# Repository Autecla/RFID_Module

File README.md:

# Módulo de Leitura de cartões
Nesse módulo é feito a leitura dos cartões RFID através de uma matriz de leitores formada por 4 leitores RFID e 1 Arduino pro mini, que envia as informações dos cartões para o módulo de controle e comunicação, via serial.

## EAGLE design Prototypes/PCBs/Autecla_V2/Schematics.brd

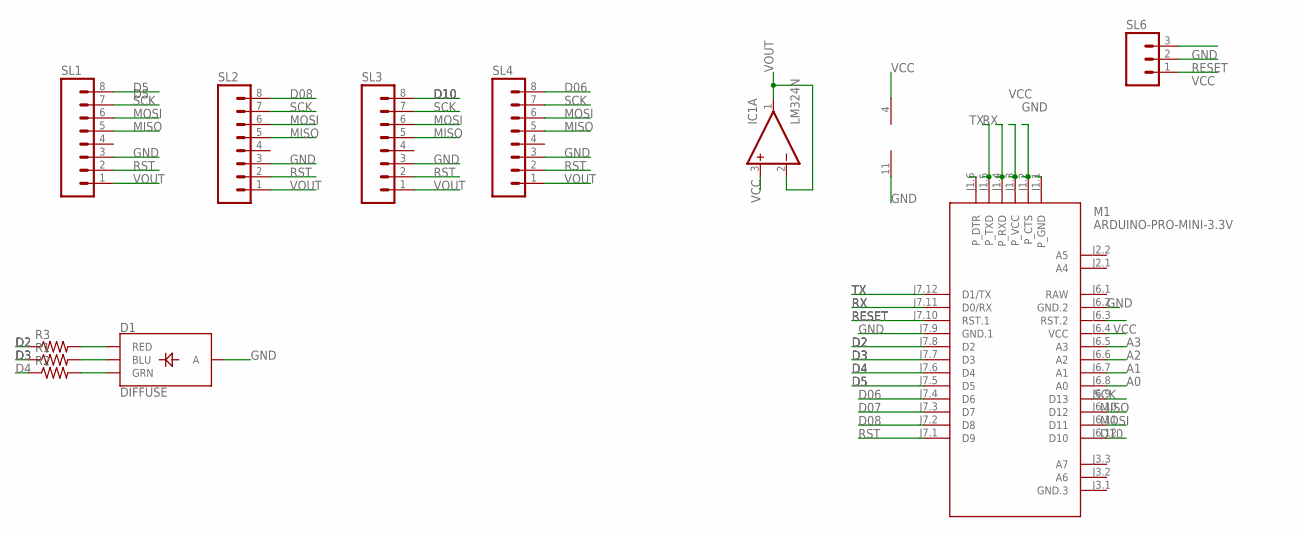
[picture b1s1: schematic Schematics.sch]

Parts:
D1: DIFFUSE; LED-RGB-THRU
IC1: LM324N; DIL14
M1: ARDUINO-PRO-MINI-3.3V; ARDUINO-PRO-MINI
R1, R2, R3: R-US_0204/7; 0204/7
SL1, SL2, SL3, SL4: M08; 08P
SL6: M03; 03P

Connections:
A0: M1.J6.8 (A0)
A1: M1.J6.7 (A1)
A2: M1.J6.6 (A2)
A3: M1.J6.5 (A3)
D2: M1.J7.8 (D2), R3.1
D3: M1.J7.7 (D3), R1.1
D4: M1.J7.6 (D4), R2.1
D5: M1.J7.5 (D5), SL1.8
D06: M1.J7.4 (D6), SL4.8
D07: M1.J7.3 (D7)
D08: M1.J7.2 (D8), SL2.8
D10: M1.J6.12 (D10), SL3.8
GND: D1.2 (A), IC1.11 (V-), M1.J1.2 (P_CTS), M1.J6.2 (GND.2), M1.J7.9 (GND.1), SL1.3, SL2.3, SL3.3, SL4.3, SL6.3
MISO: M1.J6.10 (D12), SL1.5, SL2.5, SL3.5, SL4.5
MOSI: M1.J6.11 (D11), SL1.6, SL2.6, SL3.6, SL4.6
unnamed: D1.1 (RED), R3.2
unnamed: D1.3 (GRN), R2.2
unnamed: D1.4 (BLU), R1.2
RAW: M1.J6.1 (RAW)
RESET: M1.J7.10 (RST.1), SL6.2
RST: M1.J7.1 (D9), SL1.2, SL2.2, SL3.2, SL4.2
RX: M1.J1.4 (P_RXD), M1.J7.11 (D0/RX)
SCK: M1.J6.9 (D13), SL1.7, SL2.7, SL3.7, SL4.7
TX: M1.J1.5 (P_TXD), M1.J7.12 (D1/TX)
VCC: IC1.3 (+IN), IC1.4 (V+), M1.J1.3 (P_VCC), M1.J6.4 (VCC), SL6.1
VOUT: IC1.1 (OUT), IC1.2 (-IN), SL1.1, SL2.1, SL3.1, SL4.1

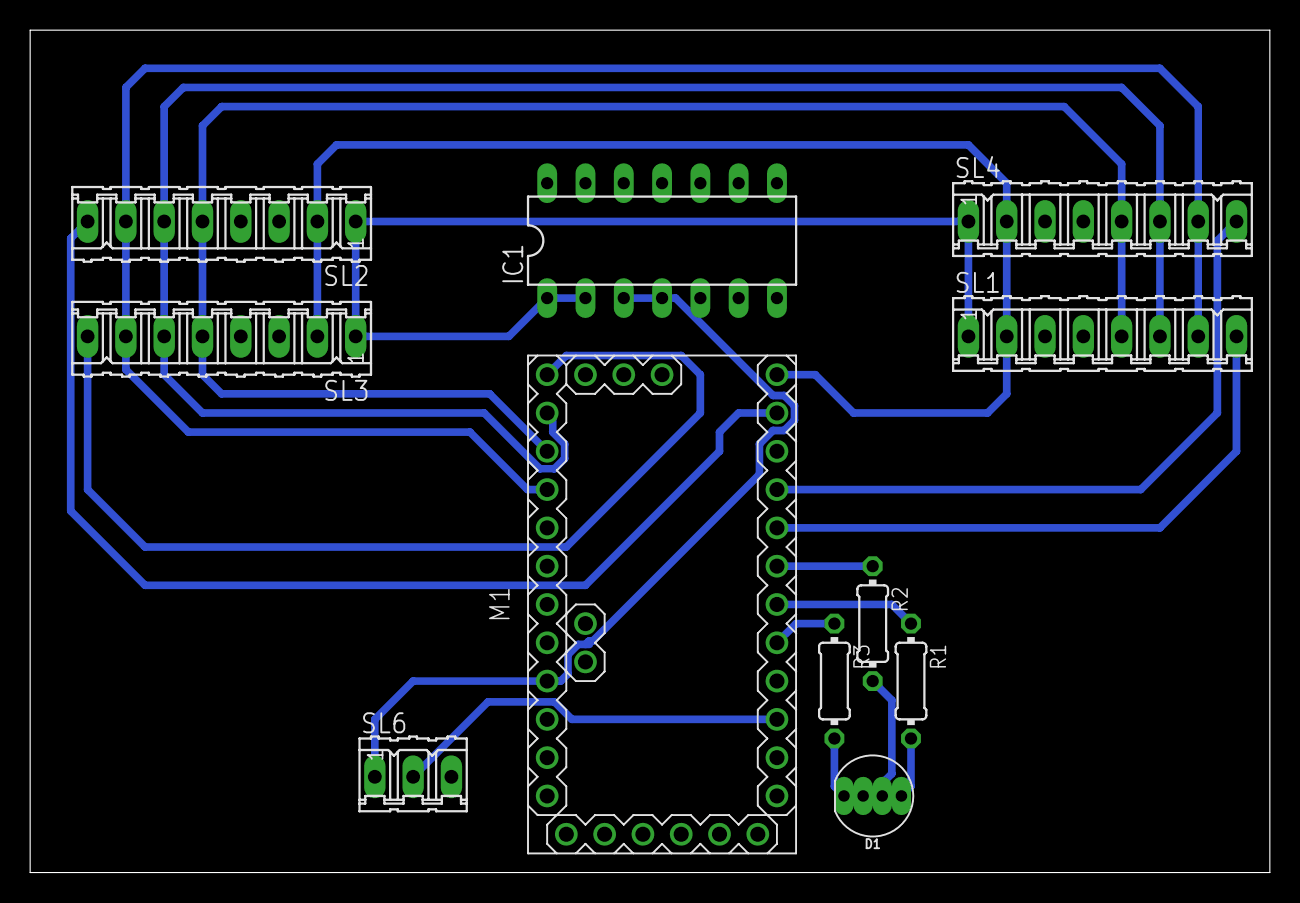
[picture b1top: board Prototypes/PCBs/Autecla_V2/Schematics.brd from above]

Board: 2 copper layers, 82.2 x 55.9 mm, 11 parts (0 on the bottom side), 20 nets.

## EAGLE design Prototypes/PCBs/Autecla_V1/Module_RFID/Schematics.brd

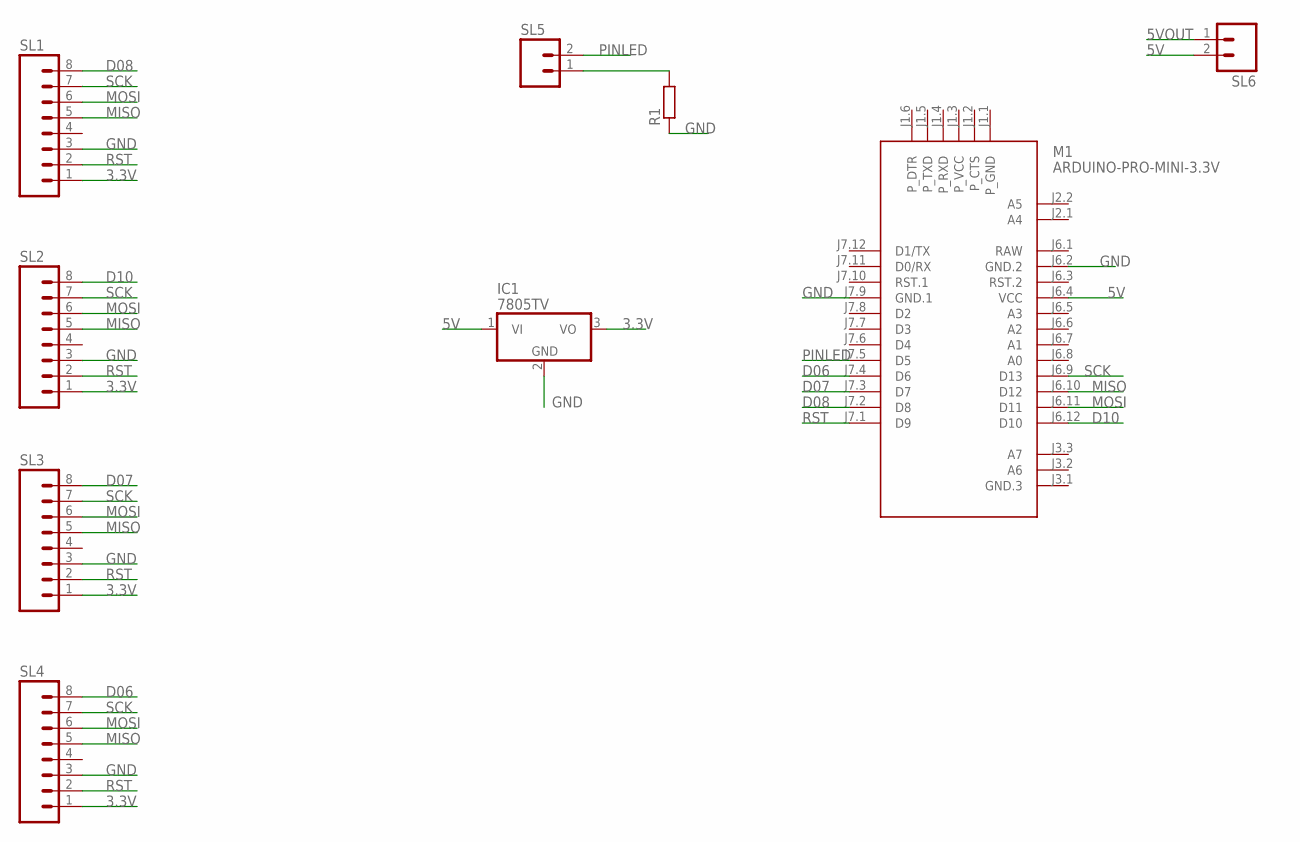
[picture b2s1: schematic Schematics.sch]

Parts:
IC1: 7805TV; TO220V
M1: ARDUINO-PRO-MINI-3.3V; ARDUINO-PRO-MINI
R1: R0204/7; 0204/7
SL1, SL2, SL3, SL4: M08; 08P
SL5, SL6: M02; 02P

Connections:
3.3V: IC1.3 (VO), SL1.1, SL2.1, SL3.1, SL4.1
5V: IC1.1 (VI), M1.J6.4 (VCC), SL6.2
5VOUT: SL6.1
D06: M1.J7.4 (D6), SL4.8
D07: M1.J7.3 (D7), SL3.8
D08: M1.J7.2 (D8), SL1.8
D10: M1.J6.12 (D10), SL2.8
GND: IC1.2 (GND), M1.J6.2 (GND.2), M1.J7.9 (GND.1), R1.1, SL1.3, SL2.3, SL3.3, SL4.3
MISO: M1.J6.10 (D12), SL1.5, SL2.5, SL3.5, SL4.5
MOSI: M1.J6.11 (D11), SL1.6, SL2.6, SL3.6, SL4.6
unnamed: R1.2, SL5.1
PINLED: M1.J7.5 (D5), SL5.2
RAW: M1.J6.1 (RAW)
RST: M1.J7.1 (D9), SL1.2, SL2.2, SL3.2, SL4.2
SCK: M1.J6.9 (D13), SL1.7, SL2.7, SL3.7, SL4.7

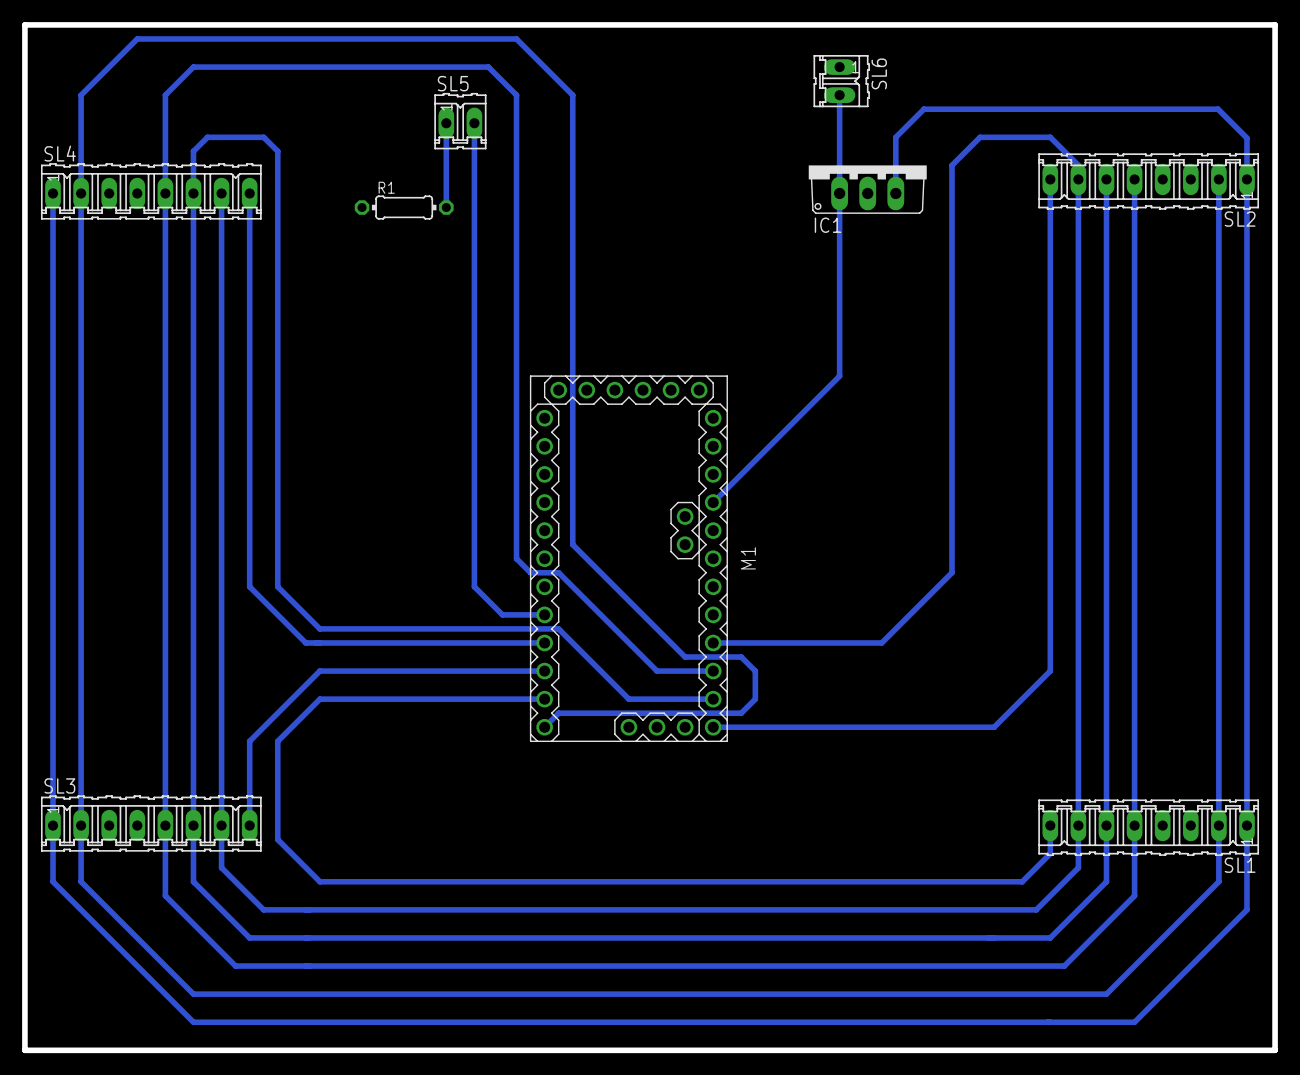
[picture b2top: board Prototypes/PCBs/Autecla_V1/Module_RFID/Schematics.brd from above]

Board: 2 copper layers, 113.0 x 92.7 mm, 9 parts (0 on the bottom side), 13 nets.

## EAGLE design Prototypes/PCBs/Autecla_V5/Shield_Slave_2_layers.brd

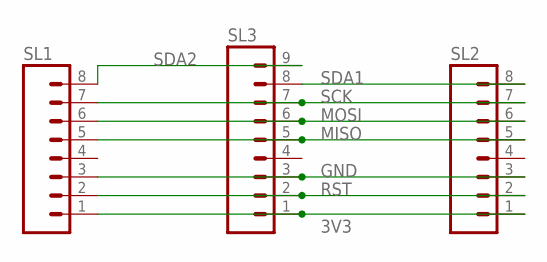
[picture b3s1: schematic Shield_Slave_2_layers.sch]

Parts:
SL1, SL2: M08; 08P
SL3: M09; 09P

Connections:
3V3: SL1.1, SL2.1, SL3.1
GND: SL1.3, SL2.3, SL3.3
MISO: SL1.5, SL2.5, SL3.5
MOSI: SL1.6, SL2.6, SL3.6
RST: SL1.2, SL2.2, SL3.2
SCK: SL1.7, SL2.7, SL3.7
SDA1: SL2.8, SL3.8
SDA2: SL1.8, SL3.9

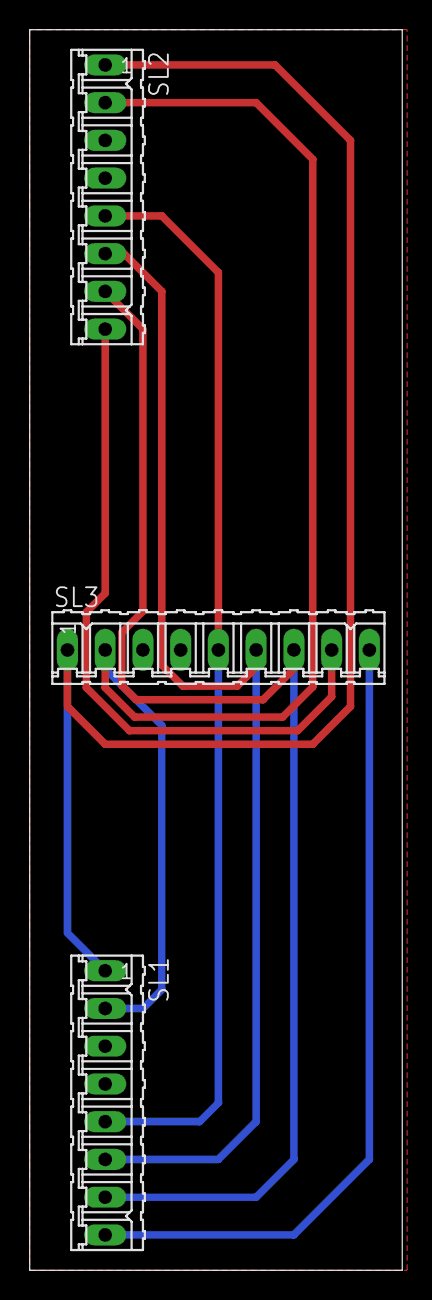
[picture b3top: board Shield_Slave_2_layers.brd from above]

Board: 2 copper layers, 25.1 x 83.5 mm, 3 parts (0 on the bottom side), 8 nets.

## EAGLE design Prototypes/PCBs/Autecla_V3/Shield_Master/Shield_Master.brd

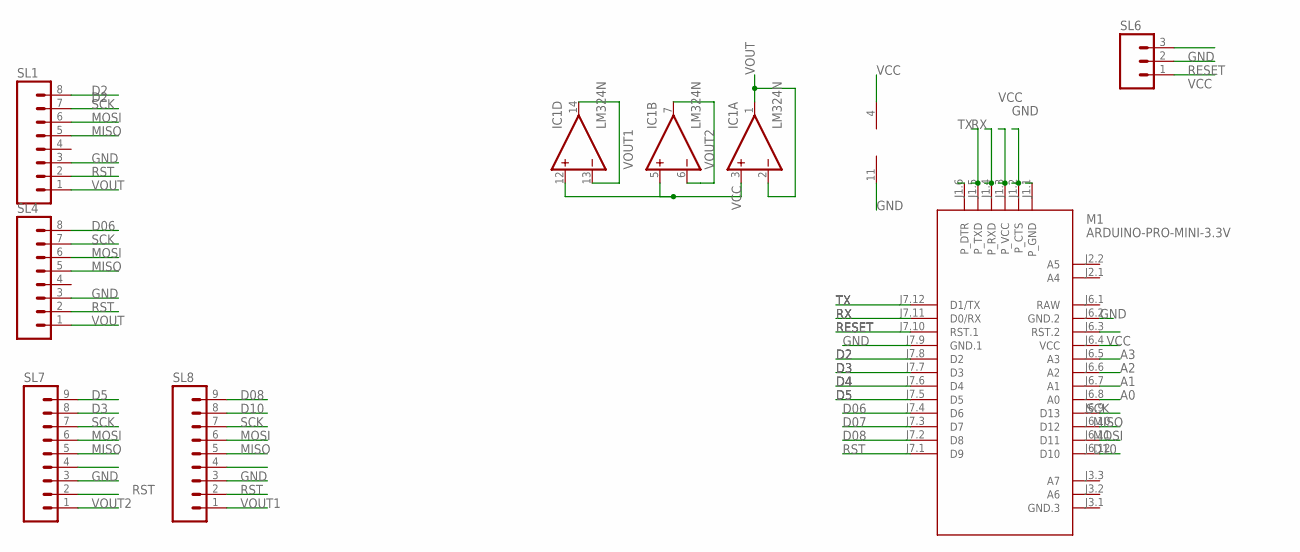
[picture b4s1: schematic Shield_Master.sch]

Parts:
IC1: LM324N; DIL14
M1: ARDUINO-PRO-MINI-3.3V; ARDUINO-PRO-MINI
SL1, SL4: M08; 08P
SL6: M03; 03P
SL7, SL8: M09; 09P

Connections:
A0: M1.J6.8 (A0)
A1: M1.J6.7 (A1)
A2: M1.J6.6 (A2)
A3: M1.J6.5 (A3)
D2: M1.J7.8 (D2), SL1.8
D3: M1.J7.7 (D3), SL7.8
D4: M1.J7.6 (D4)
D5: M1.J7.5 (D5), SL7.9
D06: M1.J7.4 (D6), SL4.8
D07: M1.J7.3 (D7)
D08: M1.J7.2 (D8), SL8.9
D10: M1.J6.12 (D10), SL8.8
GND: IC1.11 (V-), M1.J1.2 (P_CTS), M1.J6.2 (GND.2), M1.J7.9 (GND.1), SL1.3, SL4.3, SL6.3, SL7.3, SL8.3
MISO: M1.J6.10 (D12), SL1.5, SL4.5, SL7.5, SL8.5
MOSI: M1.J6.11 (D11), SL1.6, SL4.6, SL7.6, SL8.6
RAW: M1.J6.1 (RAW)
RESET: M1.J7.10 (RST.1), SL6.2
RST: M1.J7.1 (D9), SL1.2, SL4.2, SL7.2, SL8.2
RX: M1.J1.4 (P_RXD), M1.J7.11 (D0/RX)
SCK: M1.J6.9 (D13), SL1.7, SL4.7, SL7.7, SL8.7
TX: M1.J1.5 (P_TXD), M1.J7.12 (D1/TX)
VCC: IC1.3 (+IN), IC1.4 (V+), IC1.5 (+IN), IC1.12 (+IN), M1.J1.3 (P_VCC), M1.J6.4 (VCC), SL6.1
VOUT: IC1.1 (OUT), IC1.2 (-IN), SL1.1, SL4.1
VOUT1: IC1.13 (-IN), IC1.14 (OUT), SL8.1
VOUT2: IC1.6 (-IN), IC1.7 (OUT), SL7.1

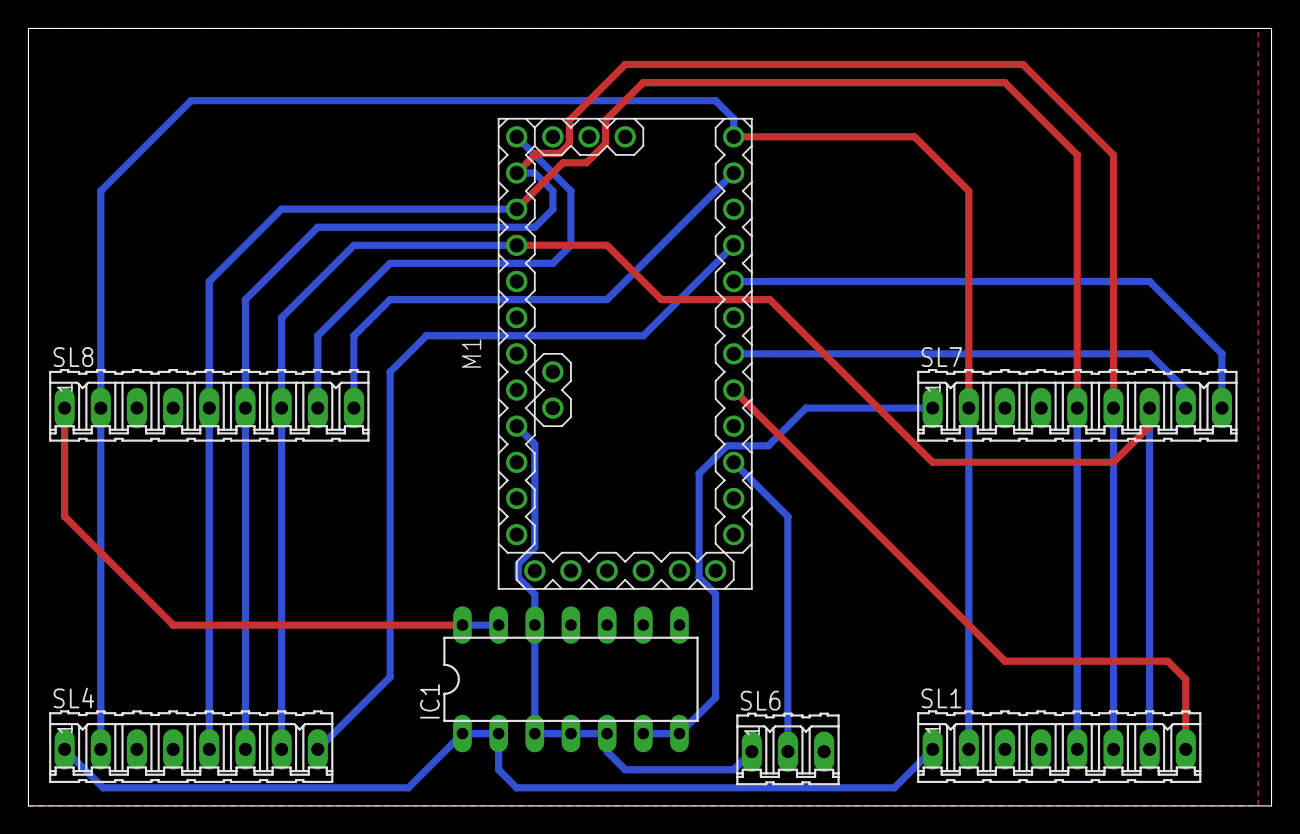
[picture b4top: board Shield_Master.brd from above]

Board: 2 copper layers, 87.3 x 54.6 mm, 7 parts (0 on the bottom side), 18 nets.

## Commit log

2018-09-18 Leitores funcionando em paralelo, falta leds!
2018-09-22 Programa teste para funcionamento dos LEDs
2018-09-22 Biblioteca do Sensor RFID
2018-09-22 Organize
2018-09-22 Programas de teste
2018-09-22 Acende LED correspondente ao leitor, ao ler Tag
2018-09-22 Módulo RFID pronto!
2018-10-02 Atualização de biblioteca
2018-10-02 Retirada de prints na biblioteca
2018-10-09 Programa para criação de buffer - em teste
2018-10-31 Ajuste de string para envio na Serial
2018-10-31 Ajustes de envios pela serial
2018-10-31 Ajuste de biblioteca
2019-05-02 Organizando arquivos
2019-10-31 test com uma nova tela

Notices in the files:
parts and their libraries:
diy-modules: Released under the Creative Commons Attribution 4.0 International License: http://creativecommons.org/licenses/by/4.0
SparkFun-LED: Licensing: Creative Commons ShareAlike 4.0 International - https://creativecommons.org/licenses/by-sa/4.0
